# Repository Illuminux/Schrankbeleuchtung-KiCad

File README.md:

# 💡 Schrankbeleuchtung

Automatisierte LED-Beleuchtung für Schränke, basierend auf einem Raspberry Pi Pico W. Türsensoren aktivieren bei Öffnung die zugeordneten LED-Gruppen über MOSFET-Schaltungen.

---

## 🧩 Features

- Bis zu 4 separat schaltbare LED-Gruppen
- Automatische Steuerung über Magnetsensoren oder Reed-Schalter
- Versorgung mit 12 V DC, intern auf 5 V und 3.3 V geregelt
- Geringe Standby-Leistung durch Low-RDS(on)-MOSFETs
- Erweiterbare Anschlüsse über XH-Steckerleisten

---

## 🔌 GPIO-Belegung (Pico W)

| Funktion         | GPIO     |
|------------------|----------|
| LED 1 (Q1)       | GPIO02   |
| LED 2 (Q2)       | GPIO04   |
| LED 3 (Q3)       | GPIO05   |
| LED 4 (Q4)       | GPIO06   |
| Sensor 1         | GPIO06   |
| Sensor 2         | GPIO07   |
| Sensor 3         | GPIO14   |
| Sensor 4         | GPIO15   |

---

## 🛠 Komponenten (Auszug)

| Bauteil      | Typ / Wert              | Bestellnummer (Mouser)  |
|--------------|-------------------------|--------------------------|
| A1           | Raspberry Pi Pico W     | 358-SC0918               |
| U1           | TPS560430XDBVT          | 595-TPS560430XDBVT       |
| Q1–Q4        | IRLML0030TRPBF          | 942-IRLML0030TRPBF       |
| R1–R4        | 187 Ω Widerstände       | 667-ERA-6AEB1870V        |
| R5–R9        | 10 kΩ Pull-Ups          | 667-ERA-6APB103V         |
| C1–C3        | 10 µF / 22 µF / 0.1 µF  | siehe BOM                |
| L1           | 10 µH Spule             | 81-LQH44PN100MPRL        |
| J2–J9        | XH-Stecker + Buchsen    | 306-B2B-XH-AMLFSNP       |

Die vollständige Stückliste befindet sich in [Schrankbeleuchtung.xlsx](Schrankbeleuchtung.xlsx)

---

## ⚙️ Inbetriebnahme

1. Platine bestücken (nach Schaltplan aus *Schrankbeleuchtung.pdf*)
2. 12 V Versorgung an J1 anschließen
3. Türsensoren an J2–J5, LEDs an J6–J9 verbinden
4. Firmware auf Pico W flashen (z. B. mit MicroPython)
5. Funktion testen – bei Türöffnung sollten zugehörige LEDs leuchten

---

## 🧠 Firmware-Hinweise

Die Firmware sollte:

- LED-GPIOs als Output setzen
- Sensor-GPIOs mit Pull-Up und Debounce abfragen
- Bei erkanntem Öffnungssignal LEDs aktivieren
- Optional: MQTT-/WLAN-Anbindung via Pico W realisieren

---

## ⚖️ Lizenz

Dieses Projekt steht unter der MIT-Lizenz. Feel free to modify, use & share!

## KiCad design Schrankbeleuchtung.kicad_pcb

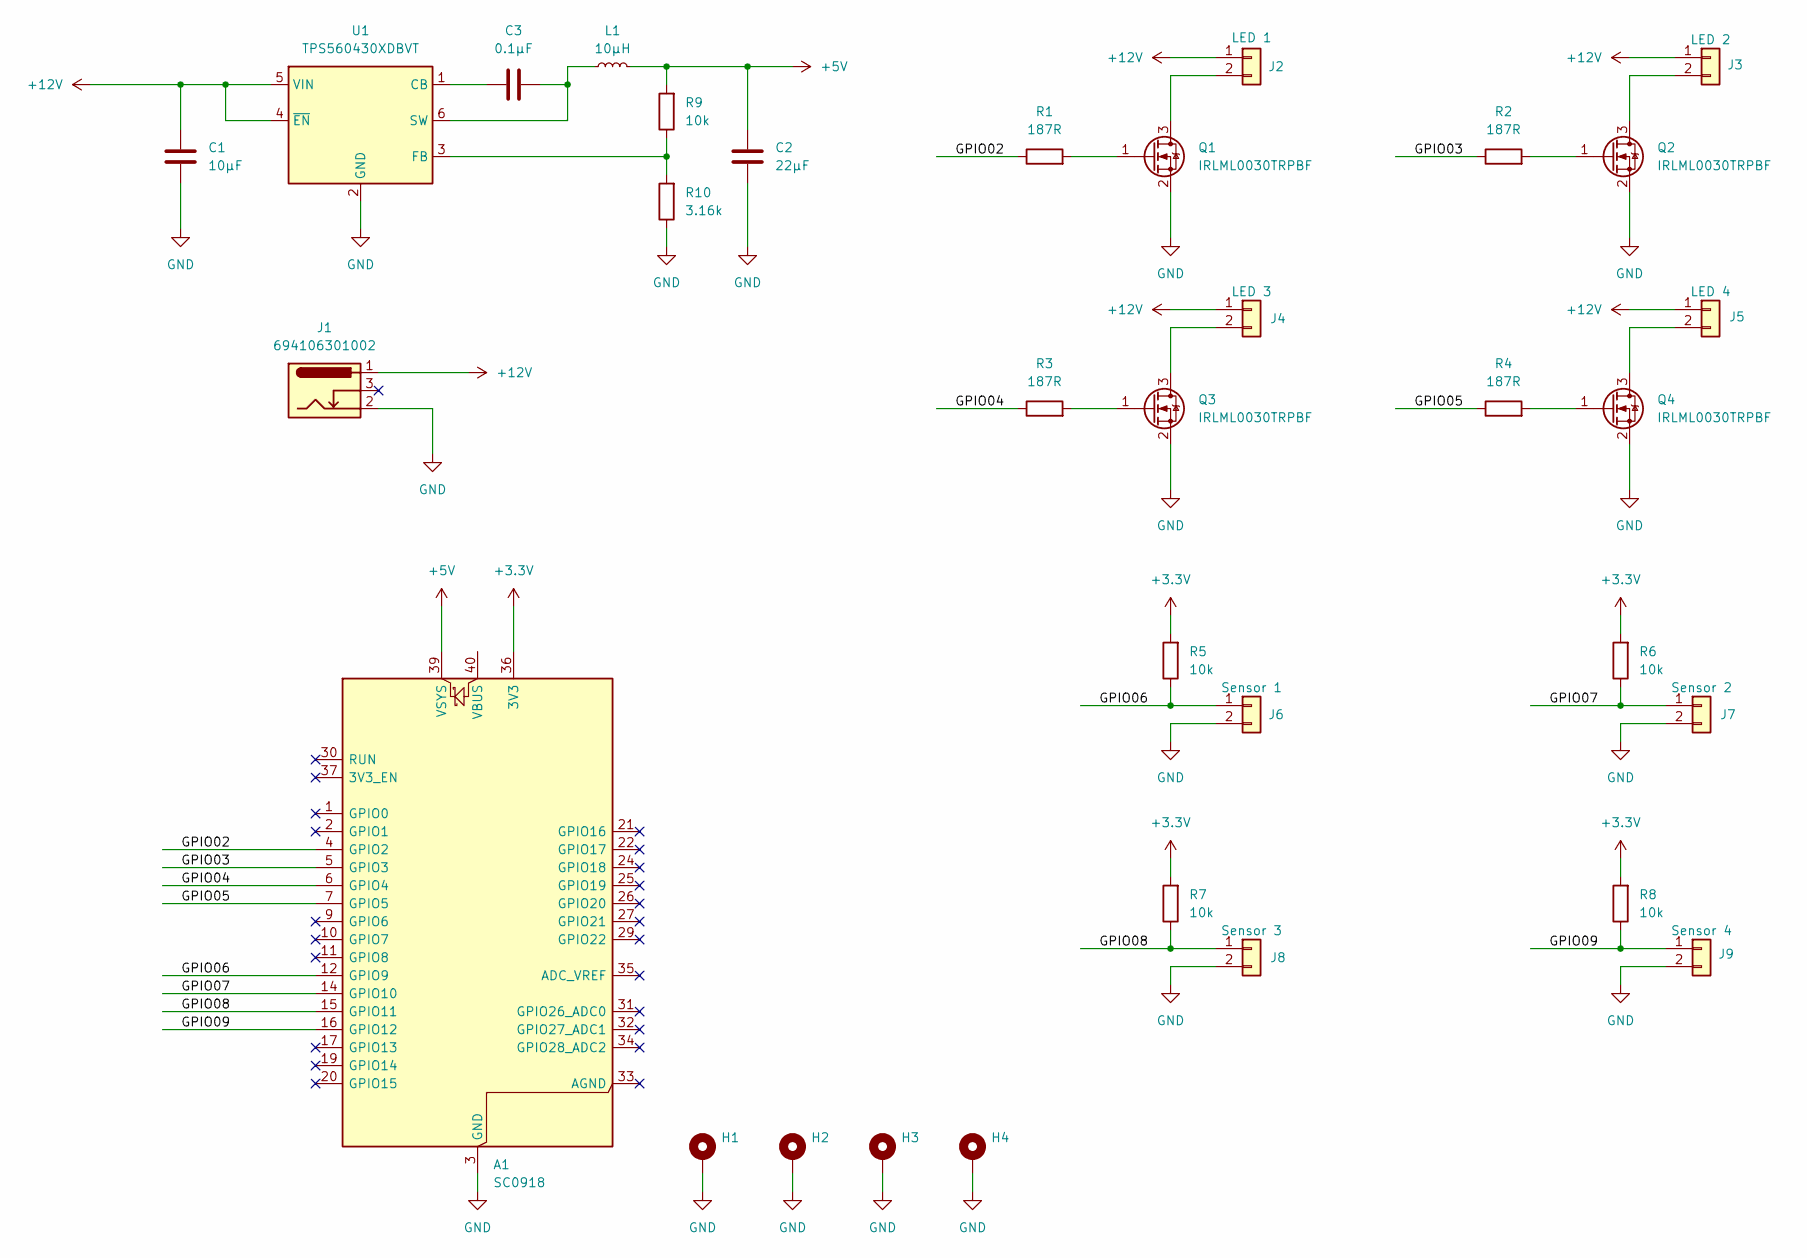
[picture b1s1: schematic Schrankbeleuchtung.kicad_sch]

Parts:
A1: SC0918; RaspberryPi_Pico_Common_THT
C1: 10µF; C_0805_2012Metric_Pad1.18x1.45mm_HandSolder; Mouser 81-GRM21BZ71E106KE5K
C2: 22µF; C_0805_2012Metric_Pad1.18x1.45mm_HandSolder; Mouser 81-GRM21BZ71A226ME5L
C3: 0.1µF; C_0805_2012Metric_Pad1.18x1.45mm_HandSolder; Mouser 581-0805ZC104JAT2A
H1, H2, H3, H4: MountingHole_Pad; MountingHole_2.2mm_M2_ISO7380_Pad
J1: 694106301002; BarrelJack_Horizontal
J2, J3, J4, J5, J6, J7, J8, J9: B2B-XH-AMLFSNP; JST_XH_B2B-XH-A_1x02_P2.50mm_Vertical
L1: 10µH; L_Cenker_CKCS4030; Mouser 81-LQH44PN100MPRL
Q1, Q2, Q3, Q4: IRLML0030TRPBF; SOT-23
R1, R2, R3, R4: 187R; R_0805_2012Metric_Pad1.20x1.40mm_HandSolder
R5, R6, R7, R8, R9: 10k; R_0805_2012Metric_Pad1.20x1.40mm_HandSolder
R10: 3.16k; R_0805_2012Metric_Pad1.20x1.40mm_HandSolder
U1: TPS560430XDBVT; SOT-23-6_Handsoldering; Mouser 595-TPS560430XDBVT

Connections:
+3.3V: A1.36 (3V3), R5.2, R6.2, R7.2, R8.2
+5V: A1.39 (VSYS), C2.1, L1.2, R9.2
+12V: C1.1, J1.1, J2.1, J3.1, J4.1, J5.1, U1.4 (~EN), U1.5 (VIN)
/GPIO02: A1.4 (GPIO2), R1.1
/GPIO03: A1.5 (GPIO3), R2.1
/GPIO04: A1.6 (GPIO4), R3.1
/GPIO05: A1.7 (GPIO5), R4.1
/GPIO06: A1.12 (GPIO9), J6.1, R5.1
/GPIO07: A1.14 (GPIO10), J7.1, R6.1
/GPIO08: A1.15 (GPIO11), J8.1, R7.1
/GPIO09: A1.16 (GPIO12), J9.1, R8.1
GND: A1.3 (GND), A1.8 (GND), A1.13 (GND), A1.18 (GND), A1.23 (GND), A1.28 (GND), A1.38 (GND), C1.2, C2.2, H1.1, H2.1, H3.1, H4.1, J1.2, J6.2, J7.2, J8.2, J9.2, Q1.2 (S), Q2.2 (S), Q3.2 (S), Q4.2 (S), R10.1, U1.2 (GND)
unnamed: J2.2, Q1.3 (D)
unnamed: J3.2, Q2.3 (D)
unnamed: J4.2, Q3.3 (D)
unnamed: J5.2, Q4.3 (D)
unnamed: Q1.1 (G), R1.2
unnamed: Q2.1 (G), R2.2
unnamed: Q3.1 (G), R3.2
unnamed: Q4.1 (G), R4.2
unnamed: C3.1, U1.1 (CB)
unnamed: R9.1, R10.2, U1.3 (FB)
unnamed: C3.2, L1.1, U1.6 (SW)

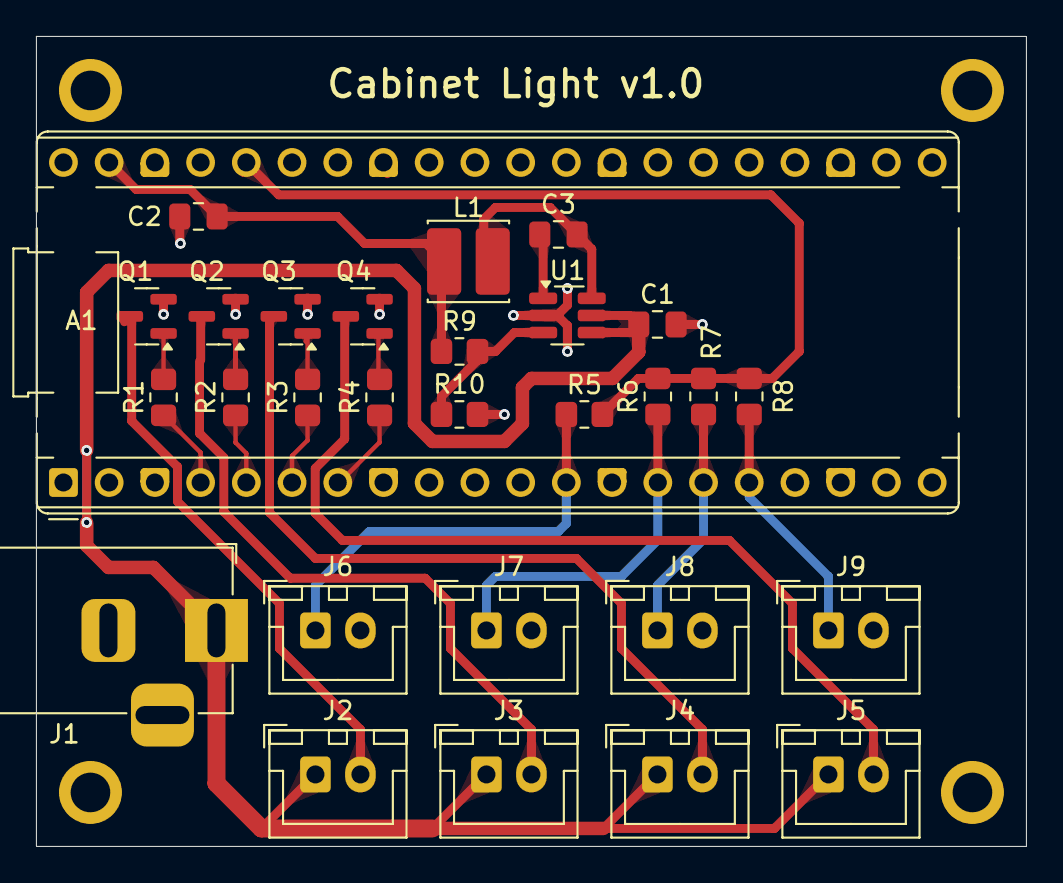
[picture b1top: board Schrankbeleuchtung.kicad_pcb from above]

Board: 2 copper layers, 55.0 x 45.0 mm, 33 parts (0 on the bottom side), 23 nets.

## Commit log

2025-06-08 Edit description
2025-06-09 Edit PCB layout
2025-06-09 Add Readme
2025-06-16 Spannungswandler geändert. Stückliste aktualisiert.
2025-06-26 PCB Layoutupdate
2025-06-26 Überarbeitung der Dokumentation
